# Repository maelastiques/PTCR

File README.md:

# PTCR -- Portable Text Communication Radio

PTCR (**Portable Text Communication Radio**) is an open hardware
LoRa-based handheld communication device designed for off‑grid
messaging.

The goal of this project is to build a **fully self‑contained radio
communicator** that can operate without cellular infrastructure,
allowing users to exchange text messages over long distances using LoRa
technology.

This project was created by **Maël**, a developer and hardware tinkerer
who enjoys:

-   hiking
-   autonomy and off‑grid systems
-   nomadic lifestyles
-   building and experimenting with electronics
-   creating whatever ideas come to mind

The idea behind PTCR came from the desire to have a **nomadic
communication tool** that works during hikes, expeditions, or remote
travel --- without relying on mobile networks.

Instead of buying a commercial device, the obvious solution was to
**build one**.

------------------------------------------------------------------------

# Device Preview

 *Front view of the device*

 *Isometric view*

 *Internal electronics*

 *Prototype board*

 *Top of the device*

 *Back of the device*

------------------------------------------------------------------------

# Features

-   **LoRa long‑range communication**
-   **GNSS positioning (GPS / GLONASS)**
-   **SPI TFT display**
-   **microSD storage**
-   **LiPo battery powered**
-   **High‑efficiency 3.3V buck regulator**
-   **Open hardware**
-   Designed for **off‑grid and nomadic use**

------------------------------------------------------------------------

# Hardware Overview

The system is built around several main components:

  Component      Role
  -------------- --------------------------
  ESP32‑S3       Main MCU
  E22‑900M22S    LoRa radio module
  Quectel L86    GNSS receiver
  MCP23017       I²C GPIO expander
  TFT display    User interface
  microSD        Data storage
  TPS62842       3.3V switching regulator
  LiPo battery   Power source
  LP5012         12 PWM canals led module
  MAX16150       switch ON/OFF with push button

The PCB uses a **4‑layer stackup**:

-   Top layer: signals
-   Internal layer: **solid ground plane**
-   Internal layer: **3.3V power plane**
-   Bottom layer: signals + ground pour

This architecture improves signal integrity and RF performance.

------------------------------------------------------------------------

# Schematic

------------------------------------------------------------------------

# Pin Mapping

## LoRa Module -- E22‑900M22S

  Signal   Direction    Description
  -------- ------------ ----------------------
  MISO     LoRa → MCU   SPI data from radio
  MOSI     MCU → LoRa   SPI data to radio
  SCK      MCU → LoRa   SPI clock
  NSS      MCU → LoRa   Chip select
  BUSY     LoRa → MCU   Radio busy indicator
  DIO1     LoRa → MCU   Interrupt
  RXEN     MCU → LoRa   Enable RX
  TXEN     MCU → LoRa   Enable TX
  NRST     MCU → LoRa   Reset

RXEN and TXEN are pulled down by default to guarantee a safe startup
state.

------------------------------------------------------------------------

## GNSS -- Quectel L86

  Signal   Direction       Description
  -------- --------------- ---------------
  TX       GNSS → MCU      NMEA output
  RX       MCU → GNSS      configuration
  V_BCKP   backup supply   RTC retention

------------------------------------------------------------------------

## MCP23017 -- GPIO Expander

Connected through **I²C**.

  Signal       Description
  ------------ ---------------
  SDA          I²C data
  SCL          I²C clock
  GPA0--GPA7   extended GPIO
  GPB0--GPB7   extended GPIO

Used for additional control signals and hardware expansion.

------------------------------------------------------------------------

## TFT Display (SPI)

  Signal   Description
  -------- ----------------
  MOSI     SPI data
  SCK      SPI clock
  CS       Chip select
  DC       Data / command
  RST      Reset
  BL       Backlight

------------------------------------------------------------------------

## microSD

  Signal   Description
  -------- -------------
  MOSI     SPI data
  MISO     SPI data
  SCK      SPI clock
  CS       Chip select

Shared SPI bus with other peripherals.

------------------------------------------------------------------------

## Leds module

  Connected through **I²C**.

  Signal       Description
  ------------ ---------------
  SDA          I²C data
  SCL          I²C clock
  OUT0-OUT11   12 PWM canals

Used for 4 RGB leds

------------------------------------------------------------------------

## ON/OFF module

  Signal       Description
  ------------ ---------------
  PB_IN        Button
  CLR          Input signal
  INT          Output signal

Used for turning ON and OFF the regulator

------------------------------------------------------------------------

# Power System

Power is supplied by a **single‑cell LiPo battery**.

A **TPS62842 buck converter** generates the **3.3V system rail**.

The design includes:

-   local decoupling capacitors
-   ferrite filtering
-   ground stitching vias
-   separated noisy power domains

This ensures stable operation for RF, GNSS, and digital circuits.

------------------------------------------------------------------------

# Firmware (planned)

The ESP32 firmware will provide:

-   LoRa messaging
-   device‑to‑device communication
-   contact management
-   message history on SD card
-   GNSS position logging
-   graphical interface on TFT

Future ideas:

-   mesh networking
-   encrypted messaging
-   APRS beacon support
-   offline mapping

------------------------------------------------------------------------

# Motivation

This project combines several things I enjoy:

-   hiking
-   autonomy and self‑reliance
-   radio communication
-   embedded electronics
-   building experimental devices

PTCR is meant to be a **portable communication device for nomadic use**,
especially when exploring places without network coverage.

And most importantly --- it was simply fun to build.

------------------------------------------------------------------------

# Project Status

Prototype stage !

Current revision: **PTCR V3**

Hardware and firmware are actively being developed.

------------------------------------------------------------------------

# Author

**Maël CUNY**

Software developer, robotics enthusiast, and hardware builder.

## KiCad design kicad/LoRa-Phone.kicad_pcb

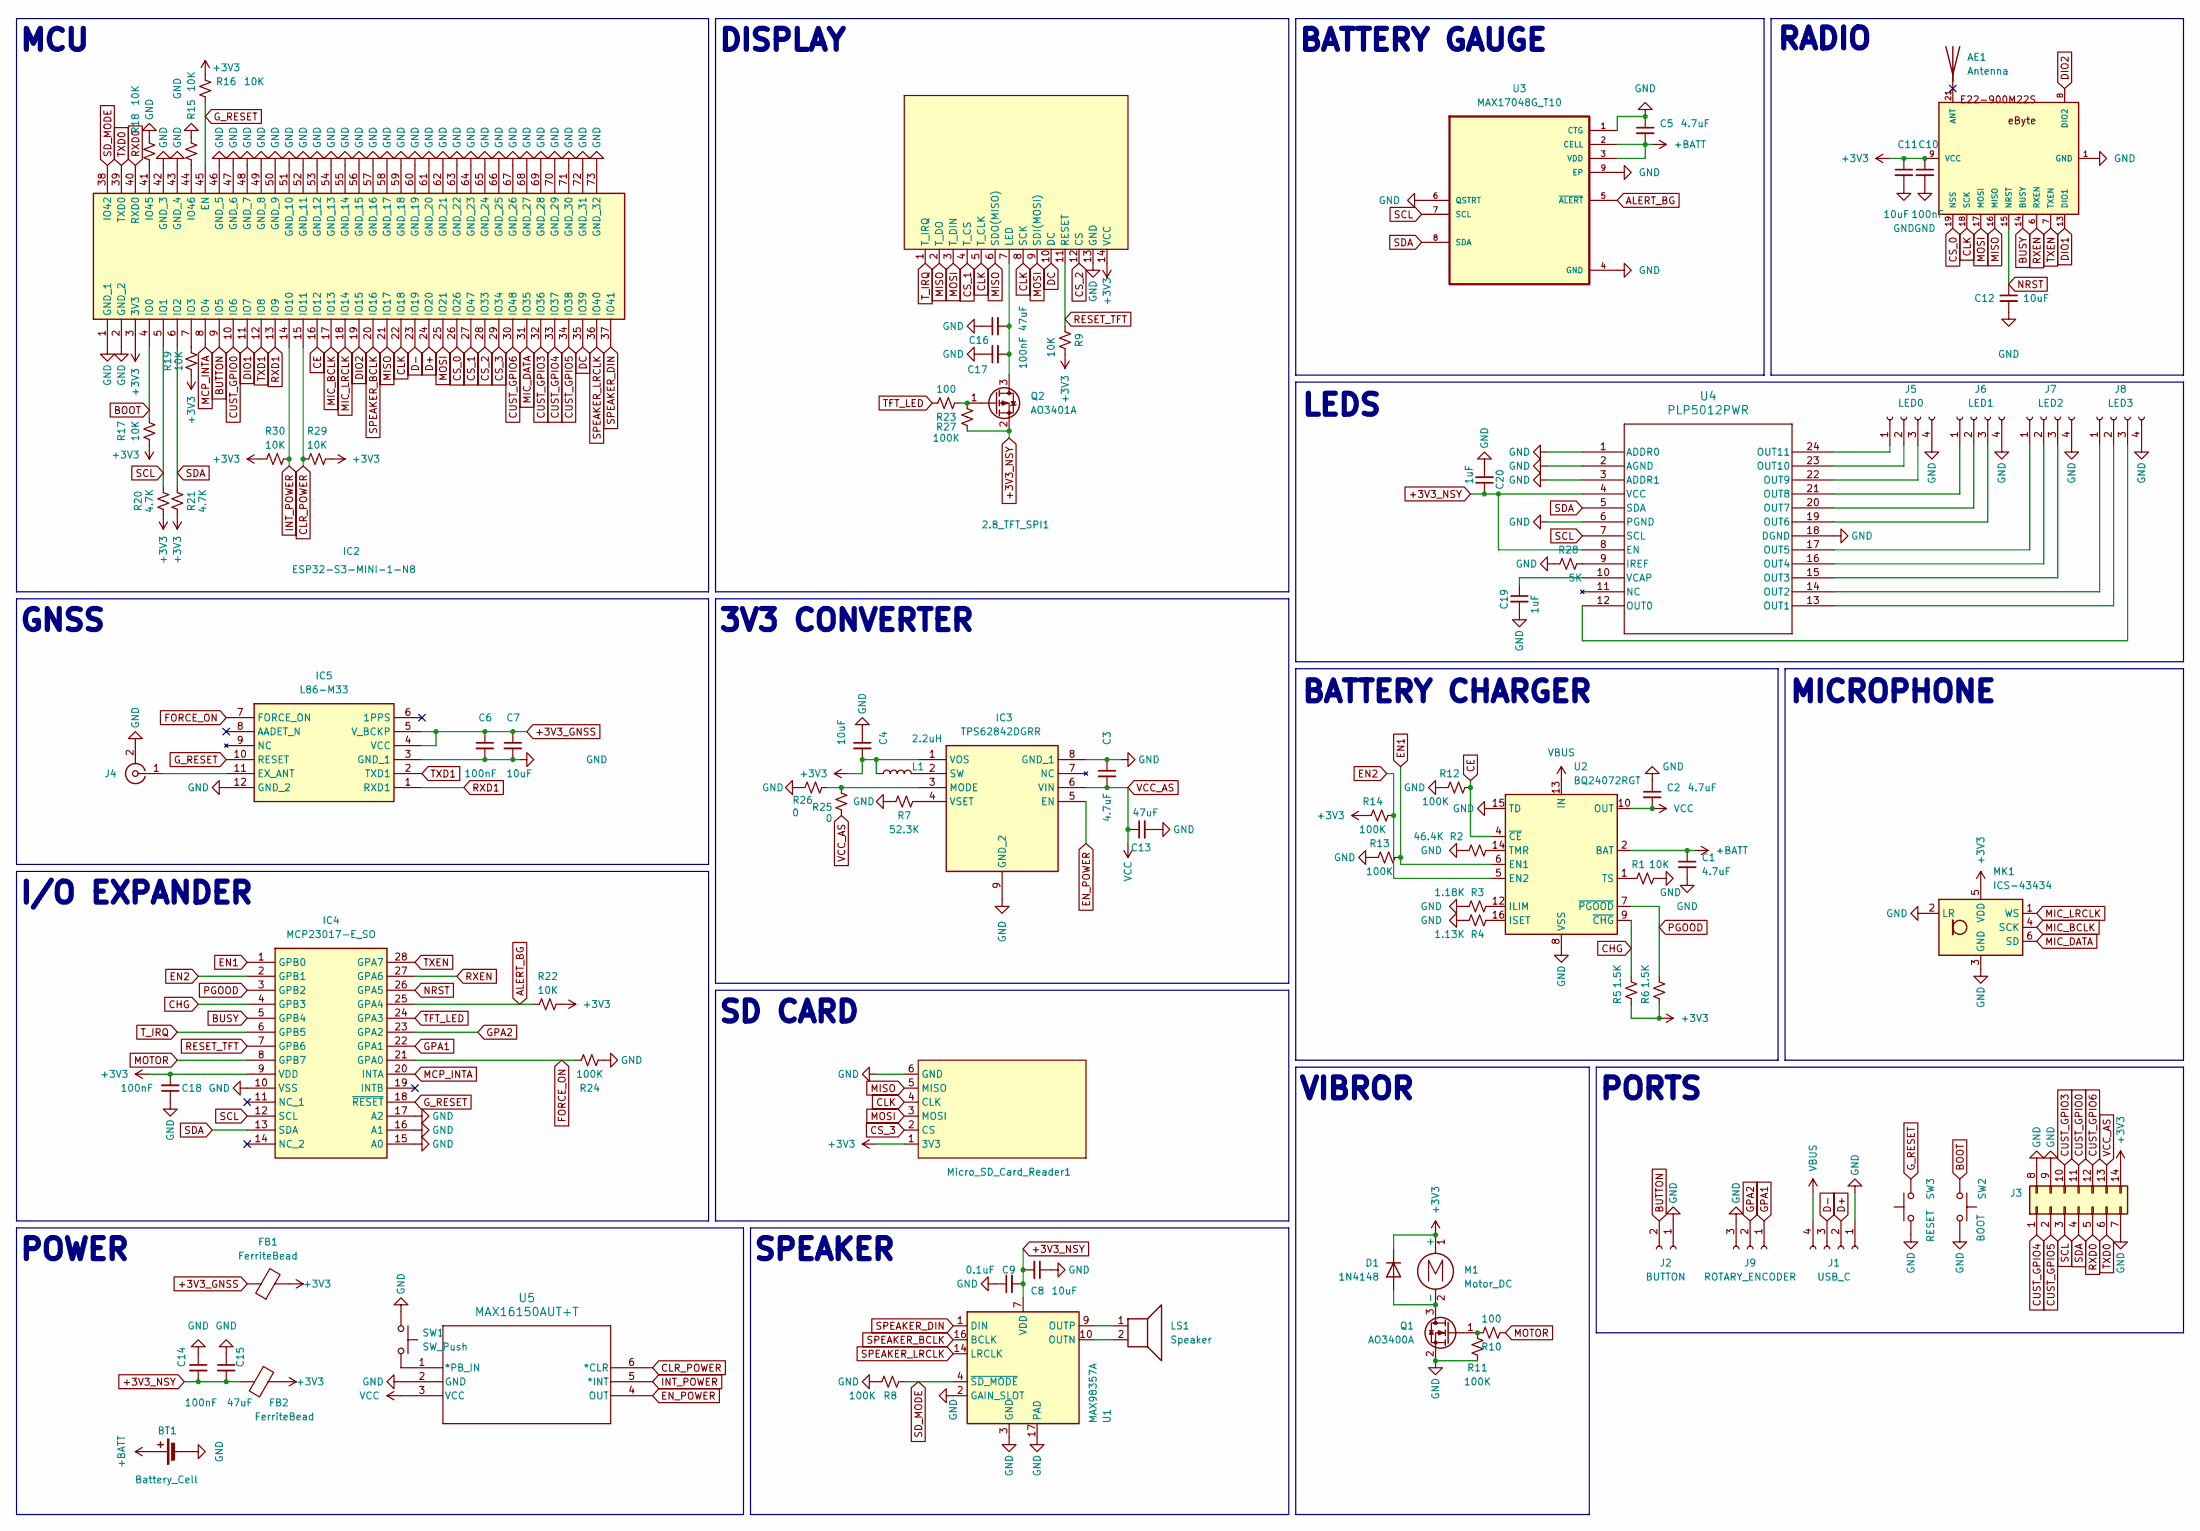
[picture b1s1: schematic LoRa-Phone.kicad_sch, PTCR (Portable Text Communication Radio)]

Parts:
2.8_TFT_SPI1: PinHeader_1x14_P2.54mm_Vertical
AE1: Antenna
BT1: Battery_Cell; SolderWire-0.1sqmm_1x02_P3.6mm_D0.4mm_OD1mm
C1, C2, C5: 4.7uF; C_0603_1608Metric
C3: 4.7uF; C_1206_3216Metric
C4: 10uF; C_0402_1005Metric
C6, C10, C14, C17, C18: 100nF; C_0603_1608Metric
C7, C8, C11, C12: 10uF; C_0603_1608Metric
C9: 0.1uF; C_0603_1608Metric
C13, C15, C16: 47uF; C_0805_2012Metric
C19, C20: 1uF; C_0603_1608Metric
D1: 1N4148; D_1206_3216Metric
FB1, FB2: FerriteBead; L_0805_2012Metric
IC1: E22-900M22S
IC2: ESP32-S3-MINI-1-N8; ESP32S3MINI1N8; Mouser Part Number 356-ESP32-S3-MINI1N8
IC3: TPS62842DGRR; SOP65P490X110-9N; Mouser Part Number 595-TPS62842DGRR
IC4: MCP23017-E_SO; SOIC127P1030X265-28N; Mouser Part Number 579-MCP23017-E/SO
IC5: L86-M33; L80-M39; Mouser Part Number 277-L86-M33
J1: USB_C; PinHeader_1x04_P1.27mm_Vertical
J2: BUTTON; PinHeader_1x02_P1.27mm_Vertical
J3: Conn_02x07_Top_Bottom; PinHeader_2x07_P1.27mm_Vertical
J4: Conn_Coaxial; U.FL_Molex_MCRF_73412-0110_Vertical
J5: LED0; PinHeader_2x02_P1.27mm_Vertical
J6: LED1; PinHeader_2x02_P1.27mm_Vertical
J7: LED2; PinHeader_2x02_P1.27mm_Vertical
J8: LED3; PinHeader_2x02_P1.27mm_Vertical
J9: ROTARY_ENCODER; PinHeader_1x03_P1.27mm_Vertical
L1: 2.2uH; L_1812_4532Metric
LS1: Speaker; PinHeader_1x02_P1.27mm_Vertical
M1: Motor_DC; PinHeader_1x02_P1.27mm_Vertical
MK1: ICS-43434; PinHeader_2x03_P1.27mm_Vertical
Micro_SD_Card_Reader1: PinHeader_1x06_P2.54mm_Vertical
Q1: AO3400A; SOT-23
Q2: AO3401A; SOT-23
R1, R9, R15, R16, R17, R18, R19, R22, R29, R30: 10K; R_0603_1608Metric
R2: 46.4K; R_0603_1608Metric
R3: 1.18K; R_0603_1608Metric
R4: 1.13K; R_0603_1608Metric
R5, R6: 1.5K; R_0603_1608Metric
R7: 52.3K; R_0603_1608Metric
R8, R11, R12, R13, R14, R24, R27: 100K; R_0603_1608Metric
R10, R23: 100; R_0603_1608Metric
R20, R21: 4.7K; R_0603_1608Metric
R25, R26: 0; R_0603_1608Metric_Pad0.98x0.95mm_HandSolder
R28: 5K; R_0603_1608Metric
SW1: SW_Push; PinHeader_1x02_P1.27mm_Vertical
SW2: BOOT; PinHeader_2x01_P1.27mm_Vertical
SW3: RESET; PinHeader_2x01_P1.27mm_Vertical
U1: MAX98357A; QFN50P300X300X100-17N-D
U2: BQ24072RGT; QFN50P300X300X100-17N-D
U3: MAX17048G_T10; SON50P200X200X80-9N
U4: PLP5012PWR; TSSOP24_PW_TEX
U5: MAX16150AUT+T; 21-0058I_MXM

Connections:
+3V3: 2.8_TFT_SPI1.14 (VCC), C4.2, C10.1, C11.1, C18.2, D1.1 (K), FB1.2, FB2.1, IC1.9 (VCC), IC2.3 (3V3), IC3.1 (VOS), IC4.9 (VDD), J3.14, L1.1, M1.1 (+), MK1.5 (VDD), Micro_SD_Card_Reader1.1 (3V3), R5.1, R6.1, R9.1, R14.1, R16.2, R17.1, R19.2, R20.1, R21.1, R22.2, R29.1, R30.1
+3V3_GNSS: C6.1, C7.1, FB1.1, IC5.4 (VCC), IC5.5 (V_BCKP)
+3V3_NSY: C8.2, C9.2, C14.2, C15.2, C20.1, FB2.2, Q2.2 (S), R27.2, U1.7 (VDD), U1.8 (VDD), U4.4 (VCC), U4.8 (EN)
+BATT: BT1.1 (+), C1.1, C5.2, U2.2 (BAT), U2.3 (BAT), U3.2 (CELL), U3.3 (VDD)
ALERT_BG: IC4.25 (GPA4), R22.1, U3.5 (~ALERT)
BOOT: IC2.4 (IO0), R17.2, SW2.1
BUSY: IC1.14 (BUSY), IC4.5 (GPB4)
BUTTON: IC2.9 (IO5), J2.2
CE: IC2.16 (IO12), R12.2, U2.4 (~CE)
CHG: IC4.4 (GPB3), R5.2, U2.9 (~CHG)
CLK: 2.8_TFT_SPI1.5 (T_CLK), 2.8_TFT_SPI1.8 (SCK), IC1.18 (SCK), IC2.22 (IO18), Micro_SD_Card_Reader1.4 (CLK)
CLR_POWER: IC2.15 (IO11), R29.2, U5.6 (*CLR)
CS_0: IC1.19 (NSS), IC2.26 (IO26)
CS_1: 2.8_TFT_SPI1.4 (T_CS), IC2.27 (IO47)
CS_2: 2.8_TFT_SPI1.12 (CS), IC2.28 (IO33)
CS_3: IC2.29 (IO34), Micro_SD_Card_Reader1.2 (CS)
CUST_GPIO0: IC2.10 (IO6), J3.11
CUST_GPIO3: IC2.32 (IO36), J3.10
CUST_GPIO4: IC2.33 (IO37), J3.1
CUST_GPIO5: IC2.34 (IO38), J3.2
CUST_GPIO6: IC2.30 (IO48), J3.12
D+: IC2.24 (IO20), J1.2
D-: IC2.23 (IO19), J1.3
DC: 2.8_TFT_SPI1.10 (DC), IC2.35 (IO39)
DIO1: IC1.13 (DIO1), IC2.11 (IO7)
DIO2: IC1.8 (DIO2), IC2.19 (IO15)
EN1: IC4.1 (GPB0), R13.2, U2.6 (EN1)
EN2: IC4.2 (GPB1), R14.2, U2.5 (EN2)
EN_POWER: IC3.5 (EN), U5.4 (OUT)
FORCE_ON: IC4.21 (GPA0), IC5.7 (FORCE_ON), R24.1
GND: 2.8_TFT_SPI1.13 (GND), BT1.2 (-), C1.2, C2.1, C3.1, C4.1, C5.1, C6.2, C7.2, C8.1, C9.1, C10.2, C11.2, C12.2, C13.2, C14.1, C15.1, C16.1, C17.1, C18.1, C19.2, C20.2, IC1.1 (GND), IC1.2 (GND), IC1.3 (GND), IC1.4 (GND), IC1.5 (GND), IC1.10 (GND), IC1.11 (GND), IC1.12 (GND), IC1.20 (GND), IC1.22 (GND), IC2.1 (GND_1), IC2.2 (GND_2), IC2.42 (GND_3), IC2.43 (GND_4), IC2.46 (GND_5), IC2.47 (GND_6), IC2.48 (GND_7), IC2.49 (GND_8), IC2.50 (GND_9), IC2.51 (GND_10), IC2.52 (GND_11), IC2.53 (GND_12), IC2.54 (GND_13), IC2.55 (GND_14), IC2.56 (GND_15), IC2.57 (GND_16), IC2.58 (GND_17), IC2.59 (GND_18), IC2.60 (GND_19), IC2.61 (GND_20), IC2.62 (GND_21), IC2.63 (GND_22), IC2.64 (GND_23), IC2.65 (GND_24), IC2.66 (GND_25), IC2.67 (GND_26), IC2.68 (GND_27), IC2.69 (GND_28), IC2.70 (GND_29), IC2.71 (GND_30), IC2.72 (GND_31), IC2.73 (GND_32), IC3.8 (GND_1), IC3.9 (GND_2), IC4.10 (VSS), IC4.15 (A0), IC4.16 (A1), IC4.17 (A2), IC5.3 (GND_1), IC5.12 (GND_2), J1.1, J2.1, J3.7, J3.8, J3.9, J4.2 (Ext), J5.4, J6.4, J7.4, J8.4, J9.3, MK1.2 (LR), MK1.3 (GND), Micro_SD_Card_Reader1.6 (GND), Q1.2 (S), R1.2, R2.1, R3.1, R4.1, R7.1, R8.2, R11.2, R12.1, R13.1, R15.2, R18.2, R24.2, R26.1, R28.2, SW1.1, SW2.2, SW3.1, U1.2 (GAIN_SLOT), U1.3 (GND), U1.11 (GND), U1.15 (GND), U1.17 (PAD), U2.8 (VSS), U2.15 (TD), U2.17 (VSS), U3.1 (CTG), U3.4 (GND), U3.6 (QSTRT), U3.9 (EP), U4.1 (ADDR0), U4.2 (AGND), U4.3 (ADDR1), U4.6 (PGND), U4.18 (DGND), U5.2 (GND)
GPA1: IC4.22 (GPA1), J9.1
GPA2: IC4.23 (GPA2), J9.2
G_RESET: IC2.45 (EN), IC4.18 (~RESET), IC5.10 (RESET), R16.1, SW3.2
INT_POWER: IC2.14 (IO10), R30.2, U5.5 (*INT)
MCP_INTA: IC2.8 (IO4), IC4.20 (INTA)
MIC_BCLK: IC2.17 (IO13), MK1.4 (SCK)
MIC_DATA: IC2.31 (IO35), MK1.6 (SD)
MIC_LRCLK: IC2.18 (IO14), MK1.1 (WS)
MISO: 2.8_TFT_SPI1.2 (T_DO), 2.8_TFT_SPI1.6 (SDO(MISO)), IC1.16 (MISO), IC2.21 (IO17), Micro_SD_Card_Reader1.5 (MISO)
MOSI: 2.8_TFT_SPI1.3 (T_DIN), 2.8_TFT_SPI1.9 (SDI(MOSI)), IC1.17 (MOSI), IC2.25 (IO21), Micro_SD_Card_Reader1.3 (MOSI)
MOTOR: IC4.8 (GPB7), R10.2
NRST: C12.1, IC1.15 (NRST), IC4.26 (GPA5)
unnamed: 2.8_TFT_SPI1.7 (LED), C16.2, C17.2, Q2.3 (D)
unnamed: AE1.1, IC1.21 (ANT)
unnamed: D1.2 (A), M1.2 (-), Q1.3 (D)
unnamed: IC2.7 (IO3), R19.1
unnamed: IC2.41 (IO45), R18.1
unnamed: IC2.44 (IO46), R15.1
unnamed: IC3.3 (MODE), R25.2, R26.2
unnamed: IC3.2 (SW), L1.2
unnamed: IC3.4 (VSET), R7.2
unnamed: IC5.11 (EX_ANT), J4.1 (In)
unnamed: J5.1, U4.24 (OUT11)
unnamed: J5.2, U4.23 (OUT10)
unnamed: J5.3, U4.22 (OUT9)
unnamed: J6.1, U4.21 (OUT8)
unnamed: J6.2, U4.20 (OUT7)
unnamed: J6.3, U4.19 (OUT6)
unnamed: J7.1, U4.17 (OUT5)
unnamed: J7.2, U4.16 (OUT4)
unnamed: J7.3, U4.15 (OUT3)
unnamed: J8.1, U4.14 (OUT2)
unnamed: J8.2, U4.13 (OUT1)
unnamed: J8.3, U4.12 (OUT0)
unnamed: Q1.1 (G), R10.1, R11.1
unnamed: Q2.1 (G), R23.2, R27.1
unnamed: LS1.2, U1.10 (OUTN)
unnamed: LS1.1, U1.9 (OUTP)
unnamed: R3.2, U2.12 (ILIM)
unnamed: R4.2, U2.16 (ISET)
unnamed: R2.2, U2.14 (TMR)
unnamed: R1.1, U2.1 (TS)
unnamed: R28.1, U4.9 (IREF)
unnamed: C19.1, U4.10 (VCAP)
unnamed: SW1.2, U5.1 (*PB_IN)
PGOOD: IC4.3 (GPB2), R6.2, U2.7 (~PGOOD)
RESET_TFT: 2.8_TFT_SPI1.11 (RESET), IC4.7 (GPB6), R9.2
RXD0: IC2.40 (RXD0), J3.5
RXD1: IC2.13 (IO9), IC5.1 (RXD1)
RXEN: IC1.6 (RXEN), IC4.27 (GPA6)
SCL: IC2.5 (IO1), IC4.12 (SCL), J3.3, R20.2, U3.7 (SCL), U4.7 (SCL)
SDA: IC2.6 (IO2), IC4.13 (SDA), J3.4, R21.2, U3.8 (SDA), U4.5 (SDA)
SD_MODE: IC2.38 (IO42), R8.1, U1.4 (~SD_MODE)
SPEAKER_BCLK: IC2.20 (IO16), U1.16 (BCLK)
SPEAKER_DIN: IC2.37 (IO41), U1.1 (DIN)
SPEAKER_LRCLK: IC2.36 (IO40), U1.14 (LRCLK)
TFT_LED: IC4.24 (GPA3), R23.1
TXD0: IC2.39 (TXD0), J3.6
TXD1: IC2.12 (IO8), IC5.2 (TXD1)
TXEN: IC1.7 (TXEN), IC4.28 (GPA7)
T_IRQ: 2.8_TFT_SPI1.1 (T_IRQ), IC4.6 (GPB5)
VBUS: J1.4, U2.13 (IN)
VCC_AS: C2.2, C3.2, C13.1, IC3.6 (VIN), J3.13, R25.1, U2.10 (OUT), U2.11 (OUT), U5.3 (VCC)

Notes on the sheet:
LEDS
VIBROR
I/O EXPANDER
DISPLAY
PORTS
RADIO
POWER
MICROPHONE
GNSS
BATTERY GAUGE
BATTERY CHARGER
SPEAKER
SD CARD
3V3 CONVERTER
MCU

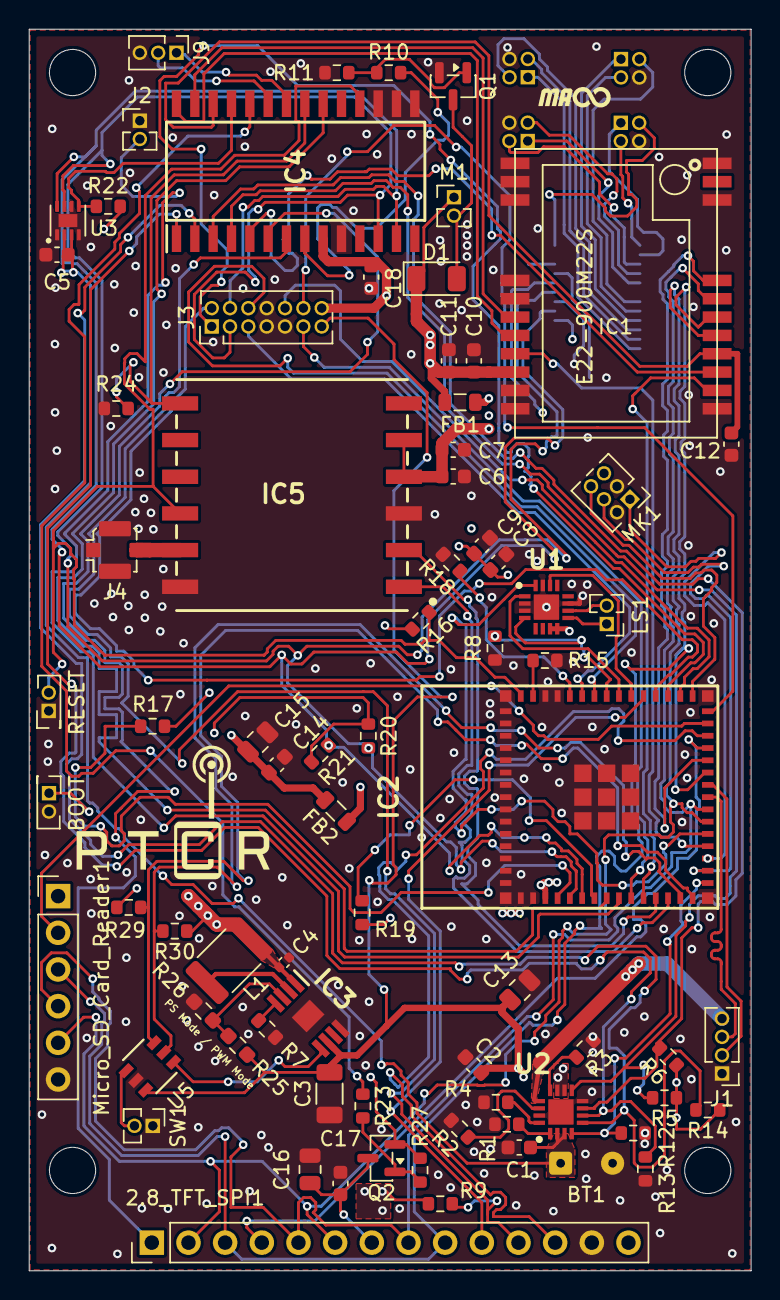
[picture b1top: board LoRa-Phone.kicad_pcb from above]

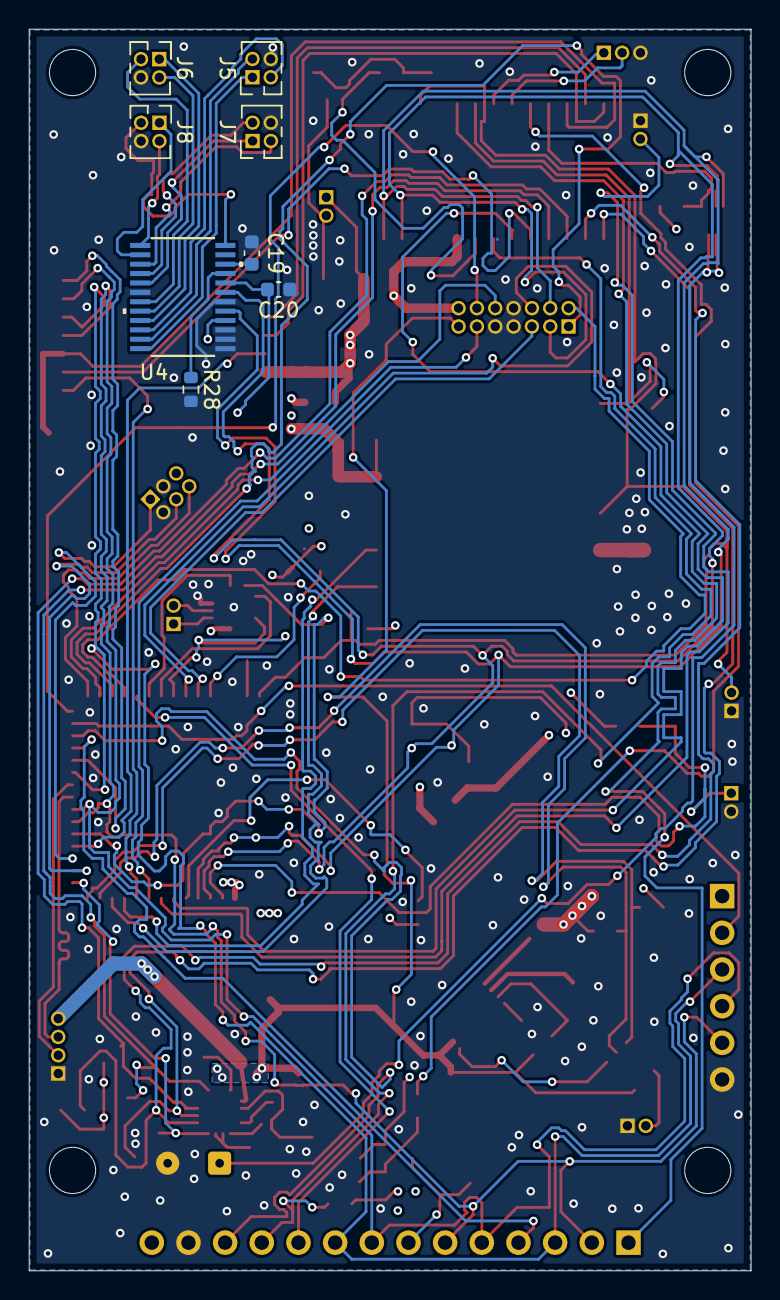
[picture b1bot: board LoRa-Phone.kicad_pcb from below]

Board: 4 copper layers, 50.0 x 86.0 mm, 88 parts (8 on the bottom side), 93 nets.

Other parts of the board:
HOLE0, HOLE1, HOLE2, HOLE3: MountingHole_3.2mm_M3

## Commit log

2026-03-16 First commit, added KiCad project and components's 3D models
2026-03-16 Added CAD and README
2026-03-16 Modified README
2026-03-30 updated images
2026-03-30 added component models
2026-03-31 release:001 Second version
2026-03-31 Second version
2026-03-31 release:100 Third version
2026-03-31 Third version
